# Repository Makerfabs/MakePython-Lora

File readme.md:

# MakePython Lora

```c++
/*
Version:		V2.1
Author:			Vincent
Create Date:	2020/7/24
Note:
2021/8/18		V2.1 Fix Lora Gateway 915M bug.
2020/12/11		V2.0 Now supply arduino lib: RadioLib
2022/8/15		V2.1 Update new RadioLib demo
*/
```

[toc]

# Makerfabs

[Makerfabs home page](https://www.makerfabs.com/)

[Makerfabs Wiki](https://wiki.makerfabs.com/)

# Introduce

The Makepython Lora transceivers feature the LoRaTM long range modem that provides ultra-long range spread spectrum communication and high interference immunity whilst minimising current consumption.

Product Link ： [MakePython Lora](https://www.makerfabs.com/esp32-lora-gateway.html)

Wiki Link : [MakePython Lora Wiki](https://wiki.makerfabs.com/MaESP_ESP32_Lora_Gateway.html)

## Front

# RadioLib Example

## send_and_receive.ino

A demo for communicating with the standard Makerfabs LoraNode (MaLora).

All Lora Nodes use this Lora library: [RadioLib](https://github.com/jgromes/RadioLib)

**It is recommended to install from Arduino Library Manager and select the library version 4.6.0. RadioLib libraries after 5.0 need to add "RADIOLIB_" before some macro definitions.**

The current firmware is developed in RadioLib 4.6.0.

## MaLora

**MaLora** is Makerfabs Loranode.

Makerfabs Lora Node is a series of products based on Arduino Pro Mini (328P) + Lora(SX127X). 

Like Relay, AC Dimmer, MOSFET, etc.

For easy to use, UID and generic instructions are provided. Some of them are our previous products, but have not added UID yet. 

[MaLora](https://github.com/Makerfabs/Makerfabs_MaLora)

*We started with MicroPython, but the Lora library support was not good. There was also a failure to communicate with other Lora libraries. So we discontinued MicroPython maintenance, and subsequent Makerfabs Lora-related products use the agreed Lora library.*

## Test

Communicates with a standard Lora Node. The code used by Maduino Lora Radio is in:

 [LoraNodeDemo](https://github.com/Makerfabs/Makerfabs_MaLora/tree/main/MaduinoLoraRadio/firmware/LoraNodeDemo)

Serial Monitor Display:

# Related Tests

- Long distance Lora communication

# Related Projects

## [Project_IoT Irrigation System](https://github.com/Makerfabs/Project_IoT-Irrigation-System)

- IoT agricultural irrigation experiment based on Lora communication.
- [YOUTUBE:Lora IoT Irrigation System - Outdoor Simulation Test](https://youtu.be/0mY6Ox0YvRk)

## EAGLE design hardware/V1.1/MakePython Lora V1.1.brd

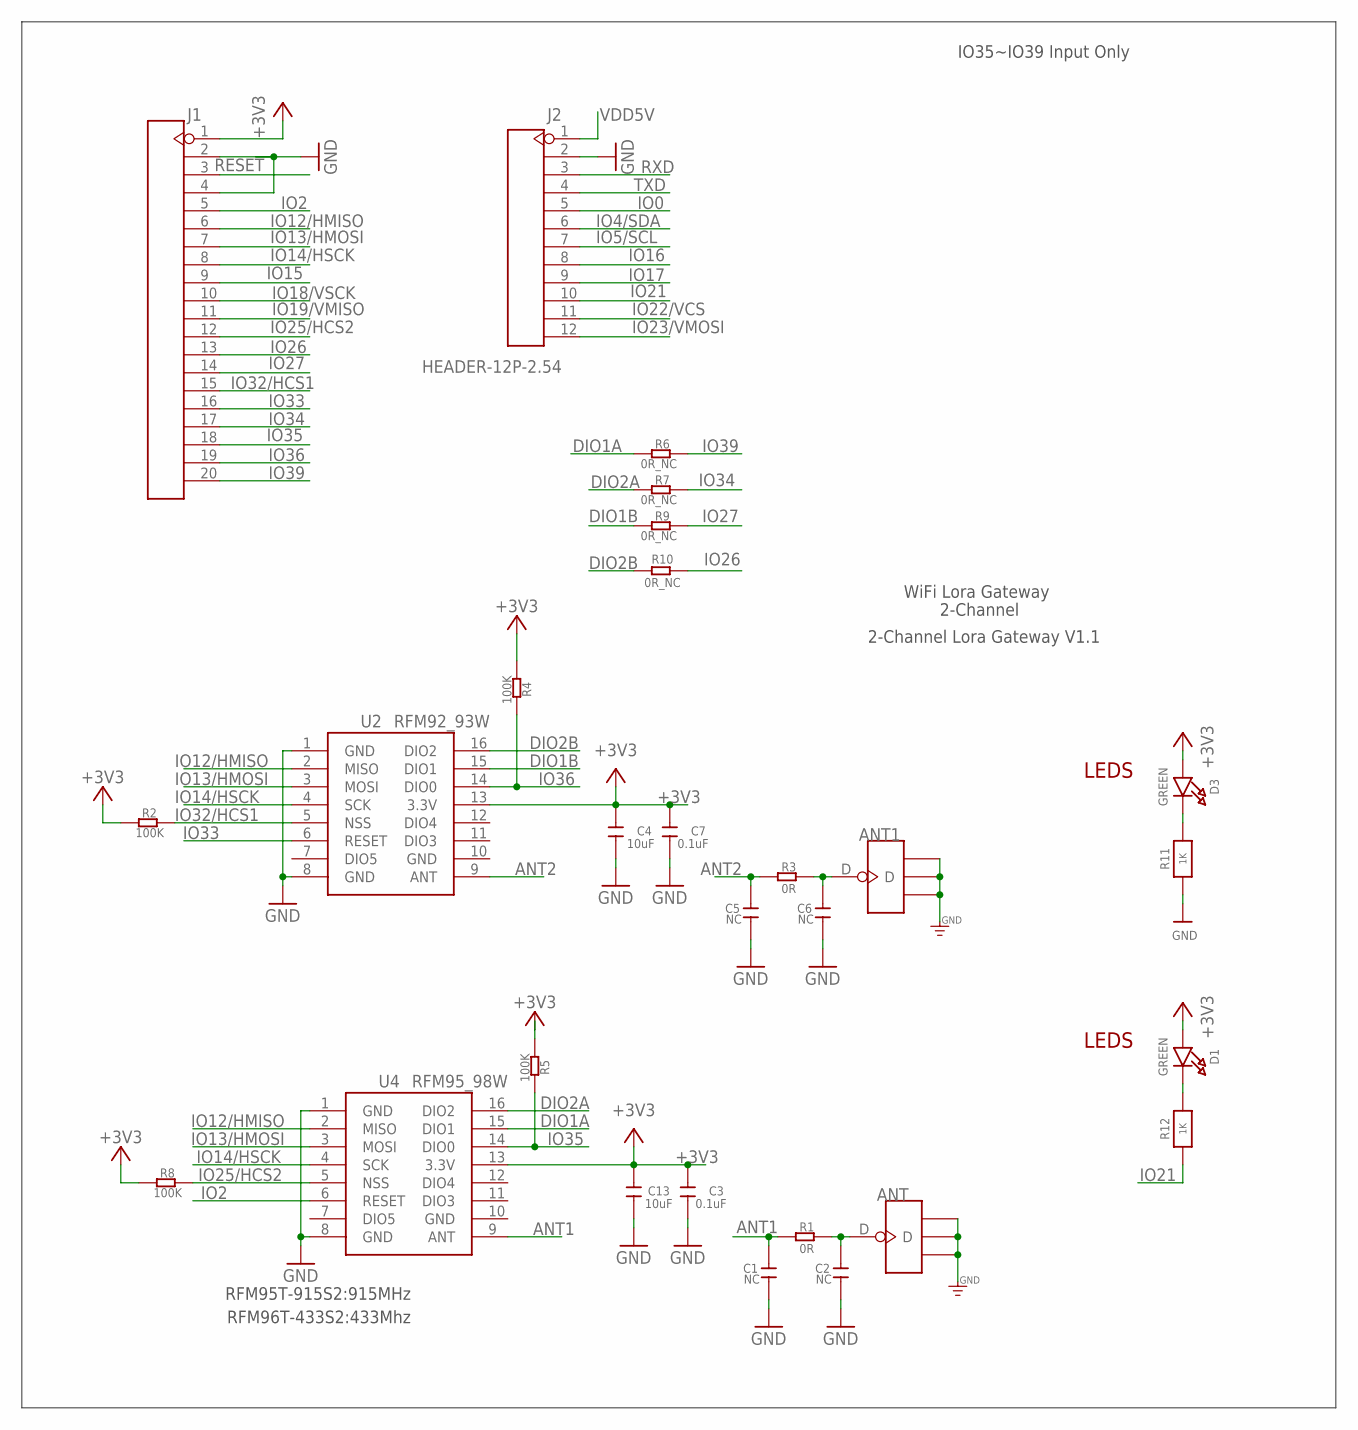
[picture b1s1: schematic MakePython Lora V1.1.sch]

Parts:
ANT, ANT1: ANTENNA-U-FL; 4P-U-FL
C1, C2, C5, C6: NC; DISCRETE_C0603
C3, C7: 0.1uF; 0603
C4, C13: 10uF; 0603
D1, D3: GREEN; CHIPLED_0805_NOOUTLINE
J1: HEADER-20P-2.54; 20P-2.54
J2: HEADER-12P-2.54; 12P-2.54
R1, R3: 0R; DISCRETE_R0603
R2, R4, R5, R8: 100K; R0603
R6, R7, R9, R10: 0R_NC; R0603
R11, R12: 1K; 0603-NO
U2: RFM92_93W
U4: RFM95_98W; RFM92_93W

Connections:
+3V3: C3.2, C4.2, C7.2, C13.2, D1.A, D3.A, J1.1, R2.2, R4.2, R5.2, R8.2, U2.13 (3.3V), U4.13 (3.3V)
ANT1: C1.2, R1.1, U4.9 (ANT)
ANT2: C5.2, R3.1, U2.9 (ANT)
DIO1A: R6.2, U4.15 (DIO1)
DIO1B: R9.2, U2.15 (DIO1)
DIO2A: R7.2, U4.16 (DIO2)
DIO2B: R10.2, U2.16 (DIO2)
GND: ANT.GND1, ANT.GND2, ANT.GND3, ANT1.GND1, ANT1.GND2, ANT1.GND3, C1.1, C2.1, C3.1, C4.1, C5.1, C6.1, C7.1, C13.1, J1.2, J1.4, J2.2, R11.1, U2.1 (GND), U2.8 (GND), U2.10 (GND), U4.1 (GND), U4.8 (GND), U4.10 (GND)
IO0: J2.5
IO2: J1.5, U4.6 (RESET)
IO4/SDA: J2.6
IO5/SCL: J2.7
IO12/HMISO: J1.6, U2.2 (MISO), U4.2 (MISO)
IO13/HMOSI: J1.7, U2.3 (MOSI), U4.3 (MOSI)
IO14/HSCK: J1.8, U2.4 (SCK), U4.4 (SCK)
IO15: J1.9
IO16: J2.8
IO17: J2.9
IO18/VSCK: J1.10
IO19/VMISO: J1.11
IO21: J2.10, R12.1
IO22/VCS: J2.11
IO23/VMOSI: J2.12
IO25/HCS2: J1.12, R8.1, U4.5 (NSS)
IO26: J1.13, R10.1
IO27: J1.14, R9.1
IO32/HCS1: J1.15, R2.1, U2.5 (NSS)
IO33: J1.16, U2.6 (RESET)
IO34: J1.17, R7.1
IO35: J1.18, R5.1, U4.14 (DIO0)
IO36: J1.19, R4.1, U2.14 (DIO0)
IO39: J1.20, R6.1
unnamed: ANT1.D, C6.2, R3.2
unnamed: ANT.D, C2.2, R1.2
unnamed: D1.C, R12.2
unnamed: D3.C, R11.2
RESET: J1.3
RXD: J2.3
TXD: J2.4
VDD5V: J2.1

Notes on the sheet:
RFM95T-915S2:915MHz
RFM96T-433S2:433Mhz
IO35~IO39 Input Only
WiFi Lora Gateway
2-Channel
2-Channel Lora Gateway V1.1
LEDS

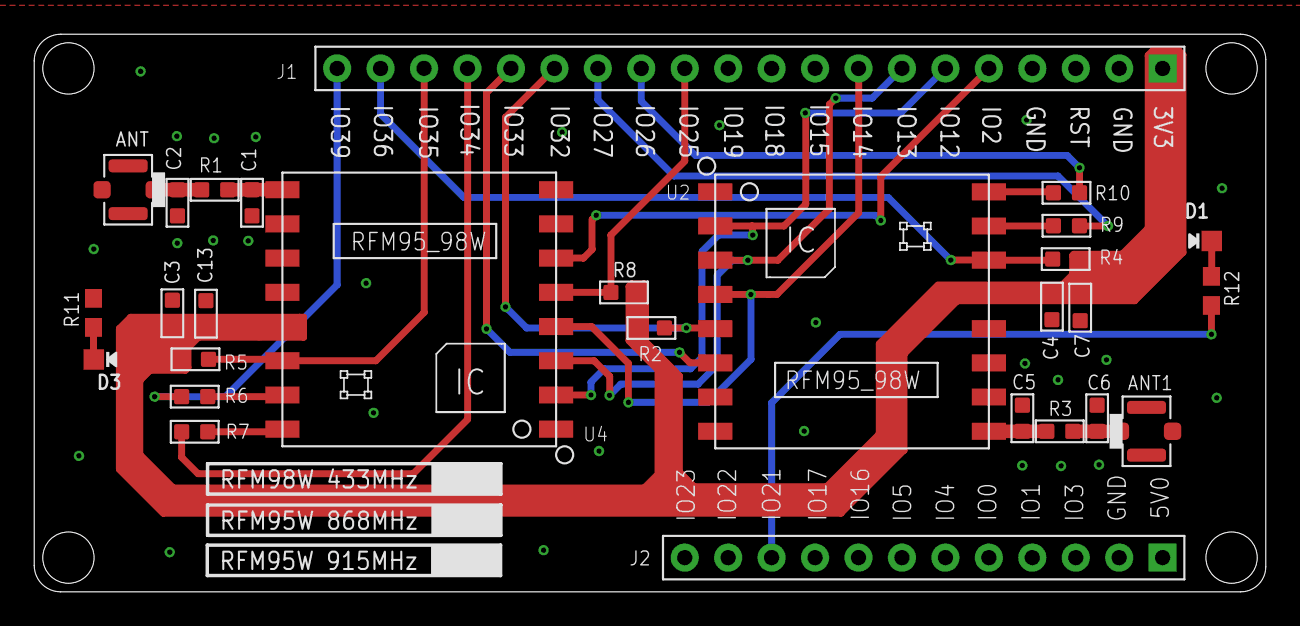
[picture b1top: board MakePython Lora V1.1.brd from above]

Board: 2 copper layers, 72.0 x 32.6 mm, 29 parts (1 on the bottom side), 26 nets.

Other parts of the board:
U$1: MAKERFABS_0.3

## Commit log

2020-05-27 Create Lora Soil Moisture Sensor
2020-05-27 Create reand
2020-05-27 Create READE
2020-05-27 Create READ
2020-07-24 create readme‘
2020-09-15 add hardware
2020-12-11 add arduino lib example
2021-08-18 Change 915 lora set
2022-02-15 hardware notice
    0Ω±5% 0603 resistors at R6,R7,R9,R10 when using RadioLib(RadioLib library requires)
2022-08-15 Update example

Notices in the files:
parts and their libraries:
microbuilder: This work is placed in the public domain, and may be freely used for commercial and non-commercial work with the following conditions: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
SparkFun-Aesthetics: Licensing: Creative Commons ShareAlike 4.0 International - https://creativecommons.org/licenses/by-sa/4.0
